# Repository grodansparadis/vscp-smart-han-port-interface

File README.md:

# vscp-smart-han-port-interface

BLE/WiFi unit to log P1 data from power meters

Still at prototype stage.

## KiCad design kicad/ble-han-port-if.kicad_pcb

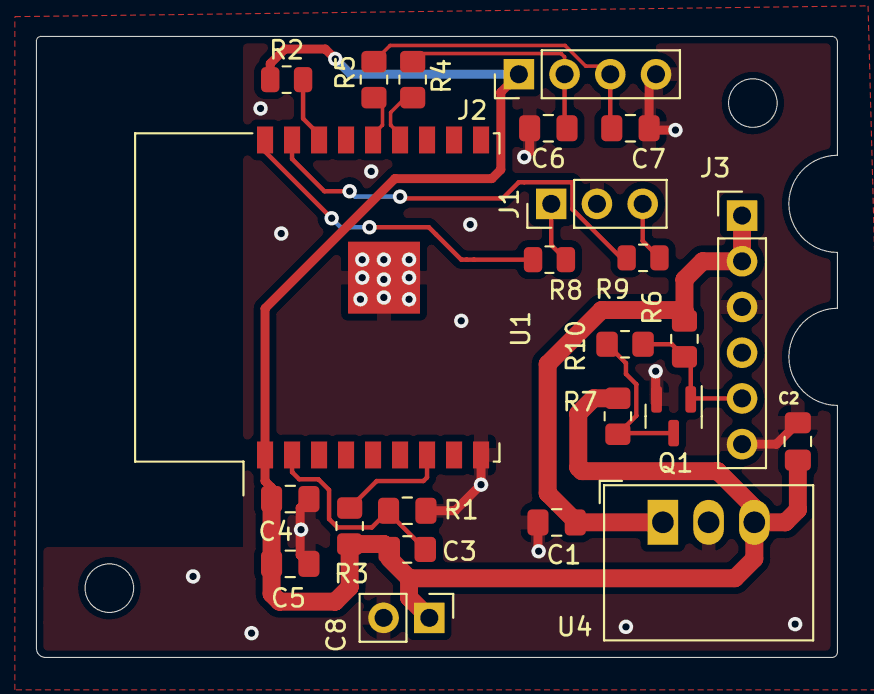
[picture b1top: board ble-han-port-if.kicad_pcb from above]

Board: 2 copper layers, 44.5 x 34.5 mm, 26 parts (0 on the bottom side), 16 nets.

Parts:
C1, C5: 10uF; C_0805_2012Metric_Pad1.18x1.45mm_HandSolder
C2, C3: 1uF; C_0805_2012Metric_Pad1.18x1.45mm_HandSolder
C4, C6, C7: 0.1uF; C_0805_2012Metric_Pad1.18x1.45mm_HandSolder
C8: C_Polarized; PinHeader_1x02_P2.54mm_Vertical
H1, H2: MountingHole; MountingHole_2.7mm_M2.5
J1: Conn_01x03; PinHeader_1x03_P2.54mm_Vertical
J2: Conn_01x04; PinHeader_1x04_P2.54mm_Vertical
J3: Conn_01x06; PinHeader_1x06_P2.54mm_Vertical
Q1: BC847; SOT-23
R1, R3: 10K; R_0805_2012Metric_Pad1.20x1.40mm_HandSolder
R2: 10K; R_0805_2012Metric
R4, R5: 27R; R_0805_2012Metric_Pad1.20x1.40mm_HandSolder
R6: 4k7; R_0805_2012Metric_Pad1.20x1.40mm_HandSolder
R7: 10k; R_0805_2012Metric_Pad1.20x1.40mm_HandSolder
R8, R9: 470; R_0805_2012Metric
R10: 0R; R_0805_2012Metric_Pad1.20x1.40mm_HandSolder
U1: ESP32-C3-WROOM-02-N4; ESP-WROOM-02
U4: R-78B3.3-1.0 (Recom); Converter_DCDC_RECOM_R-78B-2.0_THT

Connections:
+3V3: C2.1, C4.1, C5.1, C8.1, J2.1, R1.1, R2.1, R3.1, R7.2, U1.1 (3V3), U4.3 (OUT)
+5V: C1.1, J3.1, J3.2, R6.2, U4.1 (IN)
/D+: R4.1, U1.13 (IO18)
/D-: R5.1, U1.14 (IO19)
/TX: J3.5, Q1.1 (B), R6.1, R10.2
/USB D+: C7.1, J2.3, R5.2
/USB D-: C6.1, J2.2, R4.2
/leda: R8.1, U1.18 (IO0)
/ledb: R9.2, U1.17 (IO1)
/reset: C3.1, R1.2, U1.2 (EN)
GND: C1.2, C2.2, C3.2, C4.2, C5.2, C6.2, C7.2, C8.2, J1.2, J2.4, J3.3, J3.6, Q1.2 (E), U1.9 (GND), U1.19 (GND), U4.2 (GND)
unnamed: J1.1, R8.2
unnamed: J1.3, R9.1
unnamed: Q1.3 (C), R7.1, R10.1
unnamed: R2.2, U1.16 (IO2)
unnamed: R3.2, U1.7 (IO8)

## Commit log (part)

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2022-08-11 Initial checkin
2022-08-15 Test for attributes and notification
2022-10-19 Added hardware project
2022-10-19 Renamed and rearranged
2022-11-06 Rerouted USB and fixed pos for holes
2022-11-08 Added images
2022-11-08 Added note about prototype stage
2022-11-14 Renamed
